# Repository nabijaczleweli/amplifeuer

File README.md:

# [amplifeuer](https://lfs.nabijaczleweli.xyz/0017-twitter-export#1155789898718355456) 
An application of the TDA1521A, and also a boost circuit with an LT1071 because I'm a dumbass

## Schematic

## Layout

## Model

## Special thanks

To all who support further development on Patreon, in particular:

  * ThePhD

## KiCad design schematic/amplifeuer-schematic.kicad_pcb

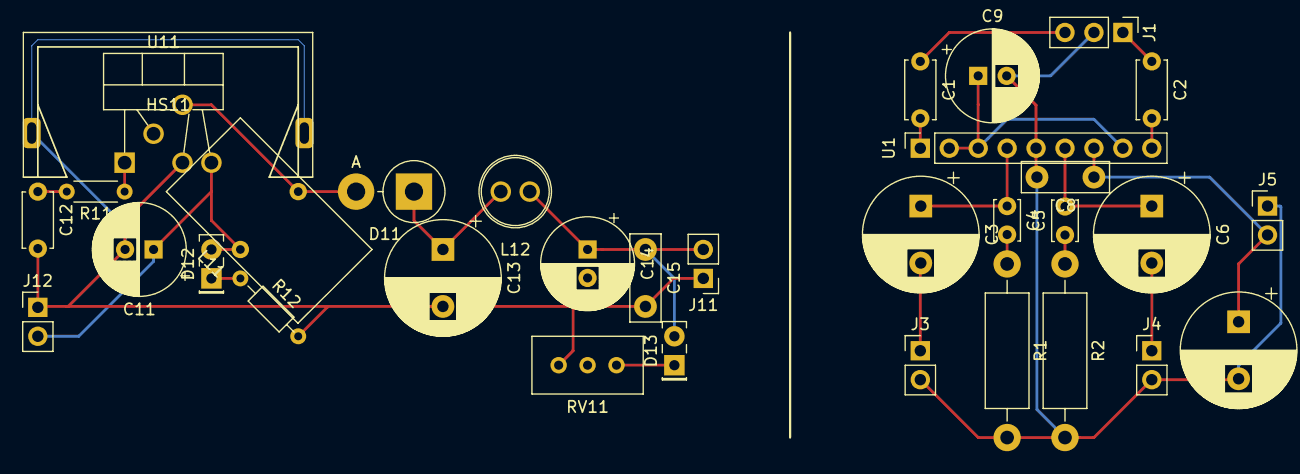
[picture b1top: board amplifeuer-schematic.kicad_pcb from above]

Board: 4 copper layers, 33 parts (0 on the bottom side), 21 nets.

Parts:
C1, C2: 220nF; C_Disc_D5.0mm_W2.5mm_P5.00mm
C3, C6, C7: 680μF; CP_Radial_D10.0mm_P5.00mm
C4, C5: 22nF; C_Disc_D3.4mm_W2.1mm_P2.50mm
C8, C15: 100nF; C_Disc_D7.5mm_W2.5mm_P5.00mm
C9, C11, C14: 100μF; CP_Radial_D8.0mm_P2.50mm
C12: 1μF; C_Disc_D4.7mm_W2.5mm_P5.00mm
C13: 1000μF; CP_Radial_D10.0mm_P5.00mm
D11: 1N5822; D_DO-201AD_P5.08mm_Vertical_AnodeUp
D12: Red; LED_Rectangular_W5.0mm_H2.0mm
D13: Green; LED_Rectangular_W5.0mm_H2.0mm
HS11: Aavid-5342B; Heatsink_Aavid-5342-TO220_Vertical
J1: Input; PinHeader_1x03_P2.54mm_Vertical
J3: Output1; PinHeader_1x02_P2.54mm_Vertical
J4: Output2; PinHeader_1x02_P2.54mm_Vertical
J5: Power; PinHeader_1x02_P2.54mm_Vertical
J11: Power out; PinHeader_1x02_P2.54mm_Vertical
J12: Power in; PinHeader_1x02_P2.54mm_Vertical
L11: 100μH; L_Toroid_Vertical_L14.5mm_W7.0mm_P7.18mm
L12: 10μH; L_Radial_D6.8mm_5.0mm_P2.54mm_sleeved
R1, R2: 10R; R_Axial_DIN0411_L9.9mm_D3.6mm_P15.24mm_Horizontal
R11: 1000R; R_Axial_DIN0204_L3.6mm_D1.6mm_P5.08mm_Horizontal
R12: 2200R; R_Axial_DIN0204_L3.6mm_D1.6mm_P7.62mm_Horizontal
RV11: 5000RTRIM; Potentiometer_Bourns_3296W_Vertical
U1: TDA1521A; PinSocket_1x09_P2.54mm_Vertical
U11: LT1071; TO-220-5_PitchAligned

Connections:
+12V: C11.1, D12.2, J12.2, L11.1, U11.5
/amplifier/+Vp: C7.1, C8.1, C14.1, C15.1, D13.2, J5.2, J11.2, L12.2, U1.7
GND: C7.2, C8.2, C9.2, C11.2, C12.2, C13.2, C14.2, C15.2, HS11.1, J1.2, J3.2, J4.2, J5.1, J11.1, J12.1, R1.2, R2.2, R12.2, RV11.1, U1.5, U11.3
unnamed: C1.1, J1.3
unnamed: C1.2, U1.1
unnamed: C2.1, J1.1
unnamed: C2.2, U1.9
unnamed: C3.1, C4.1, U1.4
unnamed: C3.2, J3.1
unnamed: C4.2, R1.1
unnamed: C5.1, R2.1
unnamed: C5.2, C6.1, U1.6
unnamed: C6.2, J4.1
unnamed: C9.1, U1.2, U1.3, U1.8
unnamed: C12.1, R11.2
unnamed: C13.1, D11.1, L12.1
unnamed: D11.2, L11.2, U11.4
unnamed: D12.1, R12.1
unnamed: D13.1, RV11.3
unnamed: R11.1, U11.1
unnamed: RV11.2, U11.2

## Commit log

2019-08-05 Add kicad-lib as submodule
2019-08-05 Add pictures/exports
2019-08-06 Add picture exports
2019-08-06 Move amplifier schematic 1 layer down
2019-08-06 Bump kicad-lib to a99b70833472ac26250ef13d11b67fb0ded32f15
2019-08-06 Add rudimentary PSU schematic and layout
2019-08-06 Concretise PSU schematic, with thanks to NimbleJack3. Add status LEDs to PSU. Add second filter stage to PSU
2019-08-09 Bump kicad-lib to 7bc52ccb37fe08f109939cb7edb4ea691a528587
2019-08-09 Stabilise components and their footprints
2019-08-09 Bump kicad-lib to 3291ebb470cdeffabf8ad952bce87863867805d5
2019-08-09 Add heatsink to PSU schematic
2019-08-09 Finalise schematic. Add schematic exports
2019-08-10 Bump kicad-lib to d8b4133738bf8f1d173f9e364e5d7737ae417f19
2019-08-10 Generate red and green LED 2x4x7mm model variants
2019-08-10 Bump kicad-lib to 23905877f31067af4f17b8f185391a477cea900b
2019-08-10 Update all models on PCB to use WRL models
2019-08-10 Lay out PSU
2019-08-10 Update exports
2019-08-11 Link to Twitter thread. I sold out
2023-07-16 Twitter link pivot

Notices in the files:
README.md:
License: MIT
